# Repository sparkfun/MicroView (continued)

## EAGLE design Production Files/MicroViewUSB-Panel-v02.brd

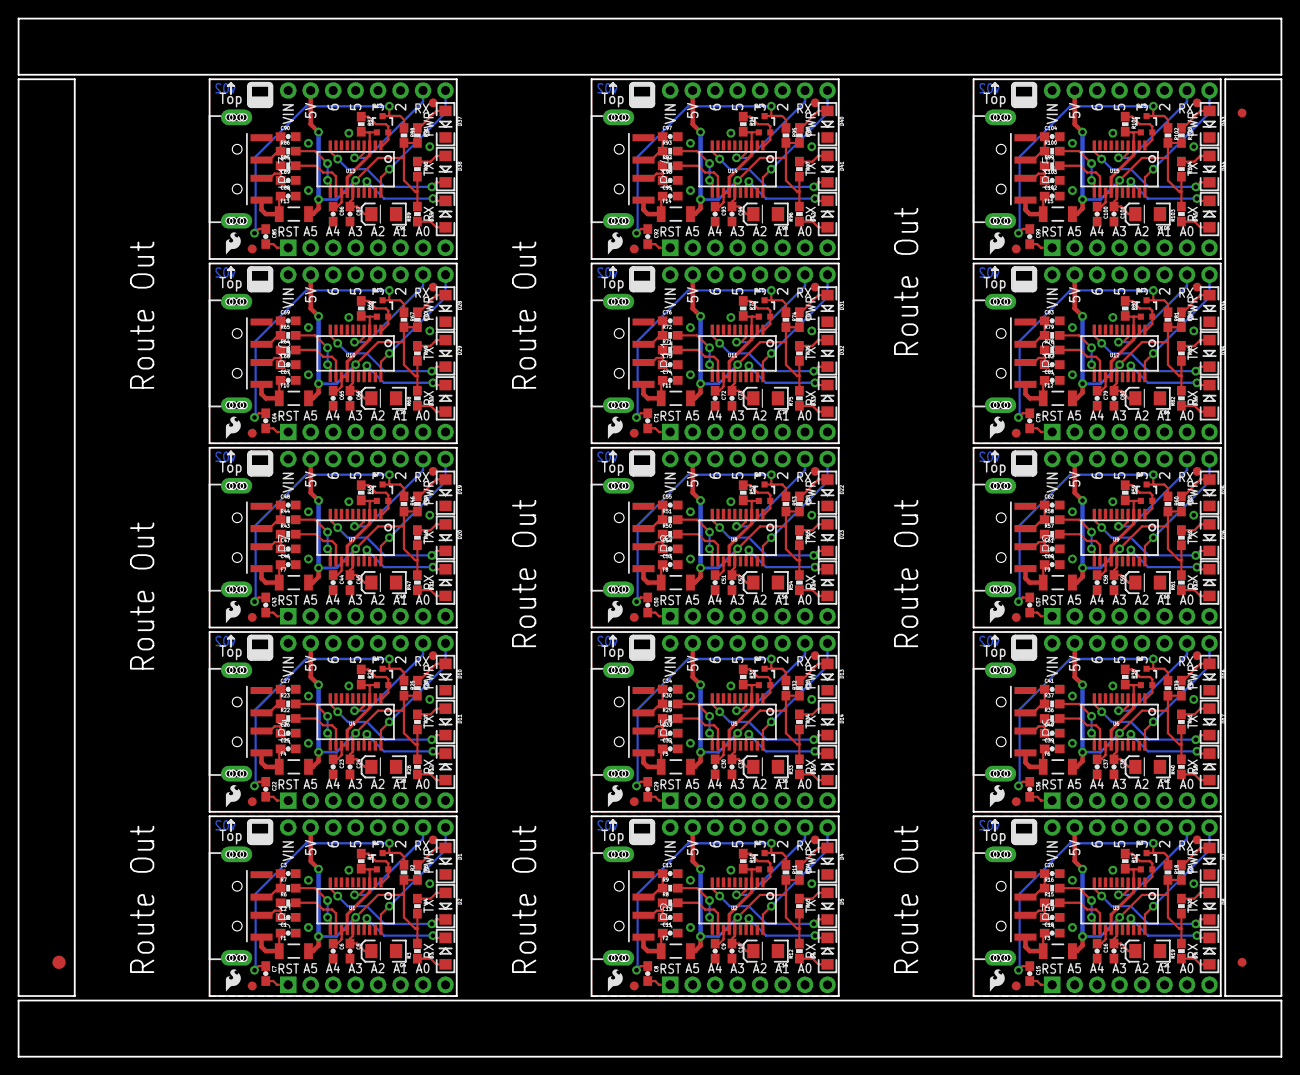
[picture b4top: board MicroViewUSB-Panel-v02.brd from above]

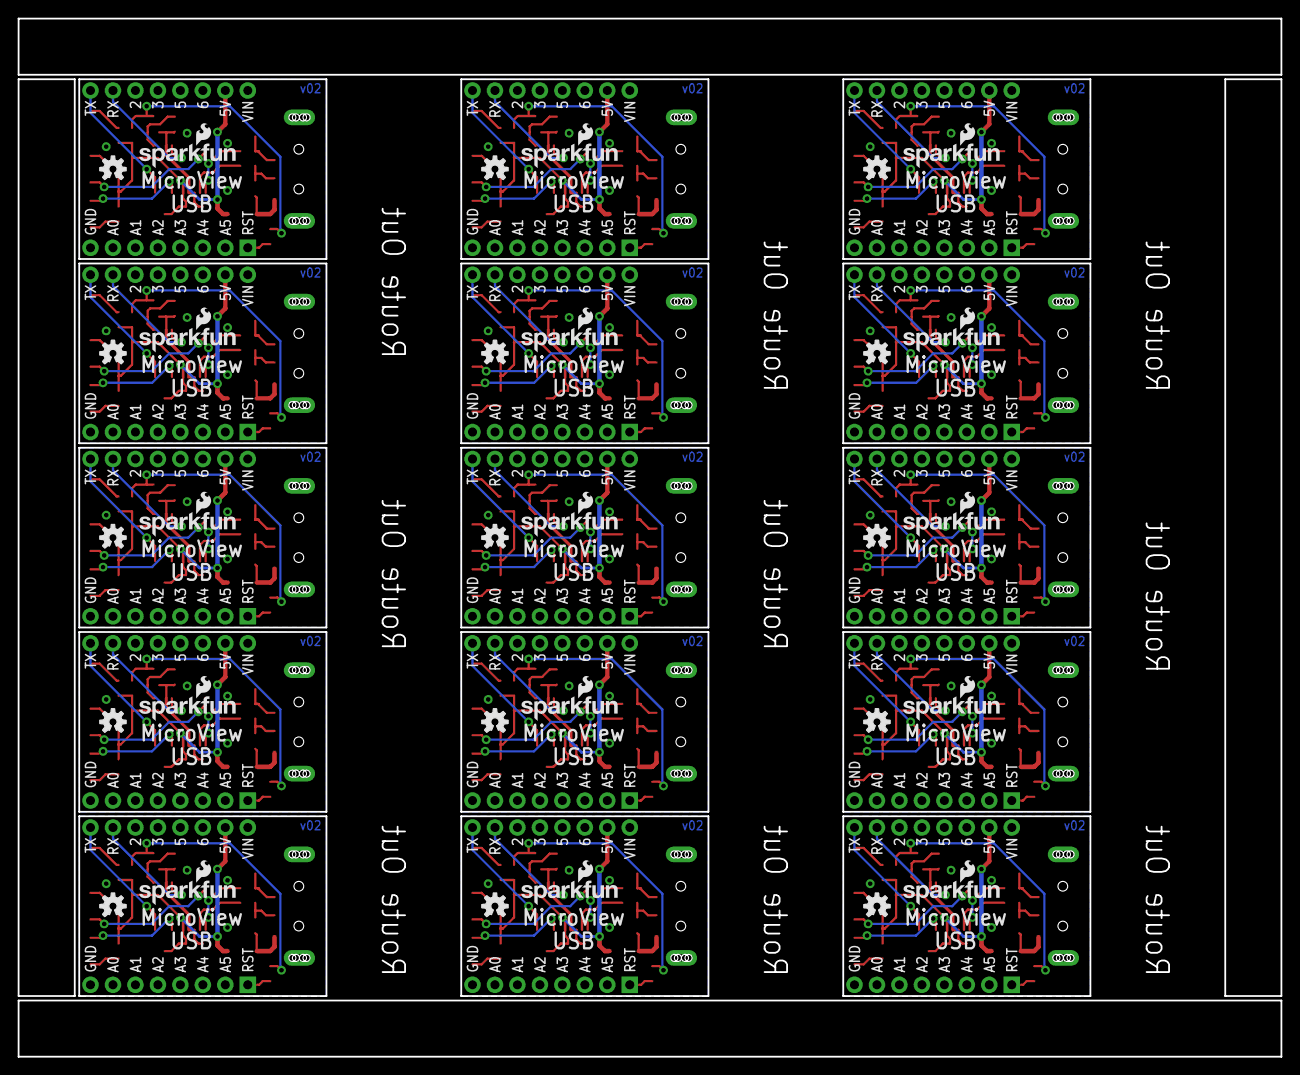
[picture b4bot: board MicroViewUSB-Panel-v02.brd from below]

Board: 2 copper layers, 142.7 x 117.3 mm, 408 parts (30 on the bottom side), 270 nets.

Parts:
C1, C5, C6, C7, C8, C9, C10, C11, C15, C16, C17, C18, C22, C23, C24, C25, C29, C30, C31, C32, C36, C37, C38, C39, C43, C44, C45, C46, C50, C51, C52, C53, C57, C58, C59, C60, C64, C65, C66, C67, C71, C72, C73, C74, C78, C79, C80, C81, C85, C86, C87, C88, C92, C93, C94, C95, C99, C100, C101, C102: 0.1uF; 0603-CAP
C2, C3, C12, C13, C19, C20, C26, C27, C33, C34, C40, C41, C47, C48, C54, C55, C61, C62, C68, C69, C75, C76, C82, C83, C89, C90, C96, C97, C103, C104: 47pF; 0603-CAP
C4, C14, C21, C28, C35, C42, C49, C56, C63, C70, C77, C84, C91, C98, C105: 10uF; EIA3216
D1, D4, D7, D10, D13, D16, D19, D22, D25, D28, D31, D34, D37, D40, D43: GREEN; LED-1206
D2, D5, D8, D11, D14, D17, D20, D23, D26, D29, D32, D35, D38, D41, D44: RED; LED-1206
D3, D6, D9, D12, D15, D18, D21, D24, D27, D30, D33, D36, D39, D42, D45: Yellow; LED-1206
E$1: FIDUCIAL-1.5X3
E$6, E$8: FIDUCIAL-1X2
F1, F2, F3, F4, F5, F6, F7, F8, F9, F10, F11, F12, F13, F14, F15: 500mA; PTC-1206-WIDE
FID1, FID2, FID3, FID4, FID5, FID6, FID7, FID8, FID9, FID10, FID11, FID12, FID13, FID14, FID15, FID16, FID17, FID18, FID19, FID20, FID21, FID22, FID23, FID24, FID25, FID26, FID27, FID28, FID29, FID30: FIDUCIAL1X2; FIDUCIAL-1X2
J1, J2, J3, J4, J5, J6, J7, J8, J9, J10, J11, J12, J13, J14, J15: MICROVIEW-16ND; MV-DIP16-NODIMENSION
JP1, JP2, JP3, JP4, JP5, JP6, JP7, JP8, JP9, JP10, JP11, JP12, JP13, JP14, JP15: USBA-SMD-MALE; USB-A-SMT-MALE
LOGO1, LOGO5, LOGO8, LOGO11, LOGO14, LOGO17, LOGO20, LOGO23, LOGO26, LOGO29, LOGO32, LOGO35, LOGO38, LOGO41, LOGO44: SFE_LOGO_FLAME.1_INCH; SFE_LOGO_FLAME_.1
LOGO2, LOGO4, LOGO7, LOGO10, LOGO13, LOGO16, LOGO19, LOGO22, LOGO25, LOGO28, LOGO31, LOGO34, LOGO37, LOGO40, LOGO43: OSHW-LOGOS; OSHW-LOGO-S
LOGO3, LOGO6, LOGO9, LOGO12, LOGO15, LOGO18, LOGO21, LOGO24, LOGO27, LOGO30, LOGO33, LOGO36, LOGO39, LOGO42, LOGO45: SFE_LOGO_NAME_FLAME.1_INCH; SFE_LOGO_NAME_FLAME_.1
Q1, Q2, Q3, Q4, Q5, Q6, Q7, Q8, Q9, Q10, Q11, Q12, Q13, Q14, Q15: 2N7002PW; SOT323
R1, R2, R10, R11, R17, R18, R24, R25, R31, R32, R38, R39, R45, R46, R52, R53, R59, R60, R66, R67, R73, R74, R80, R81, R87, R88, R94, R95, R101, R102: 10K; 0603-RES
R3, R4, R5, R12, R13, R14, R19, R20, R21, R26, R27, R28, R33, R34, R35, R40, R41, R42, R47, R48, R49, R54, R55, R56, R61, R62, R63, R68, R69, R70, R75, R76, R77, R82, R83, R84, R89, R90, R91, R96, R97, R98, R103, R104, R105: 1K; 0603-RES
R6, R7, R8, R9, R15, R16, R22, R23, R29, R30, R36, R37, R43, R44, R50, R51, R57, R58, R64, R65, R71, R72, R78, R79, R85, R86, R92, R93, R99, R100: 27; 0603-RES
U1, U2, U3, U4, U5, U6, U7, U8, U9, U10, U11, U12, U13, U14, U15: FT231XS; SSOP20_L

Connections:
3.3V: C6.1, Q1.1, R1.2, U1.3, U1.13, U1.14
3.3V1: C9.1, Q2.1, R10.2, U2.3, U2.13, U2.14
3.3V2: C16.1, Q3.1, R17.2, U3.3, U3.13, U3.14
3.3V3: C23.1, Q4.1, R24.2, U4.3, U4.13, U4.14
3.3V4: C30.1, Q5.1, R31.2, U5.3, U5.13, U5.14
3.3V5: C37.1, Q6.1, R38.2, U6.3, U6.13, U6.14
3.3V6: C44.1, Q7.1, R45.2, U7.3, U7.13, U7.14
3.3V7: C51.1, Q8.1, R52.2, U8.3, U8.13, U8.14
3.3V8: C58.1, Q9.1, R59.2, U9.3, U9.13, U9.14
3.3V9: C65.1, Q10.1, R66.2, U10.3, U10.13, U10.14
3.3V10: C72.1, Q11.1, R73.2, U11.3, U11.13, U11.14
3.3V11: C79.1, Q12.1, R80.2, U12.3, U12.13, U12.14
3.3V12: C86.1, Q13.1, R87.2, U13.3, U13.13, U13.14
3.3V13: C93.1, Q14.1, R94.2, U14.3, U14.13, U14.14
3.3V14: C100.1, Q15.1, R101.2, U15.3, U15.13, U15.14
5V: C4.A, C5.1, F1.2, J1.15, R2.2, R3.2, R4.2, R5.2, U1.15
5V1: C10.1, C14.A, F2.2, J2.15, R11.2, R12.2, R13.2, R14.2, U2.15
5V2: C17.1, C21.A, F3.2, J3.15, R18.2, R19.2, R20.2, R21.2, U3.15
5V3: C24.1, C28.A, F4.2, J4.15, R25.2, R26.2, R27.2, R28.2, U4.15
5V4: C31.1, C35.A, F5.2, J5.15, R32.2, R33.2, R34.2, R35.2, U5.15
5V5: C38.1, C42.A, F6.2, J6.15, R39.2, R40.2, R41.2, R42.2, U6.15
5V6: C45.1, C49.A, F7.2, J7.15, R46.2, R47.2, R48.2, R49.2, U7.15
5V7: C52.1, C56.A, F8.2, J8.15, R53.2, R54.2, R55.2, R56.2, U8.15
5V8: C59.1, C63.A, F9.2, J9.15, R60.2, R61.2, R62.2, R63.2, U9.15
5V9: C66.1, C70.A, F10.2, J10.15, R67.2, R68.2, R69.2, R70.2, U10.15
5V10: C73.1, C77.A, F11.2, J11.15, R74.2, R75.2, R76.2, R77.2, U11.15
5V11: C80.1, C84.A, F12.2, J12.15, R81.2, R82.2, R83.2, R84.2, U12.15
5V12: C87.1, C91.A, F13.2, J13.15, R88.2, R89.2, R90.2, R91.2, U13.15
5V13: C94.1, C98.A, F14.2, J14.15, R95.2, R96.2, R97.2, R98.2, U14.15
5V14: C101.1, C105.A, F15.2, J15.15, R102.2, R103.2, R104.2, R105.2, U15.15
D+: C3.1, JP1.D+1, R7.1
D+1: C13.1, JP2.D+1, R9.1
D+2: C20.1, JP3.D+1, R16.1
D+3: C27.1, JP4.D+1, R23.1
D+4: C34.1, JP5.D+1, R30.1
D+5: C41.1, JP6.D+1, R37.1
D+6: C48.1, JP7.D+1, R44.1
D+7: C55.1, JP8.D+1, R51.1
D+8: C62.1, JP9.D+1, R58.1
D+9: C69.1, JP10.D+1, R65.1
D+10: C76.1, JP11.D+1, R72.1
D+11: C83.1, JP12.D+1, R79.1
D+12: C90.1, JP13.D+1, R86.1
D+13: C97.1, JP14.D+1, R93.1
D+14: C104.1, JP15.D+1, R100.1
D-: C2.1, JP1.D-1, R6.1
D-1: C12.1, JP2.D-1, R8.1
D-2: C19.1, JP3.D-1, R15.1
D-3: C26.1, JP4.D-1, R22.1
D-4: C33.1, JP5.D-1, R29.1
D-5: C40.1, JP6.D-1, R36.1
D-6: C47.1, JP7.D-1, R43.1
D-7: C54.1, JP8.D-1, R50.1
D-8: C61.1, JP9.D-1, R57.1
D-9: C68.1, JP10.D-1, R64.1
D-10: C75.1, JP11.D-1, R71.1
D-11: C82.1, JP12.D-1, R78.1
D-12: C89.1, JP13.D-1, R85.1
D-13: C96.1, JP14.D-1, R92.1
D-14: C103.1, JP15.D-1, R99.1
DTR: C7.1, Q1.3, R2.1
DTR1: C8.1, Q2.3, R11.1
DTR2: C15.1, Q3.3, R18.1
DTR3: C22.1, Q4.3, R25.1
DTR4: C29.1, Q5.3, R32.1
DTR5: C36.1, Q6.3, R39.1
DTR6: C43.1, Q7.3, R46.1
DTR7: C50.1, Q8.3, R53.1
DTR8: C57.1, Q9.3, R60.1
DTR9: C64.1, Q10.3, R67.1
DTR10: C71.1, Q11.3, R74.1
DTR11: C78.1, Q12.3, R81.1
DTR12: C85.1, Q13.3, R88.1
DTR13: C92.1, Q14.3, R95.1
DTR14: C99.1, Q15.3, R102.1
GND: C1.2, C2.2, C3.2, C4.C, C5.2, C6.2, D1.C, J1.8, JP1.GND1, U1.6, U1.16
GND1: C9.2, C10.2, C11.2, C12.2, C13.2, C14.C, D4.C, J2.8, JP2.GND1, U2.6, U2.16
GND2: C16.2, C17.2, C18.2, C19.2, C20.2, C21.C, D7.C, J3.8, JP3.GND1, U3.6, U3.16
GND3: C23.2, C24.2, C25.2, C26.2, C27.2, C28.C, D10.C, J4.8, JP4.GND1, U4.6, U4.16
GND4: C30.2, C31.2, C32.2, C33.2, C34.2, C35.C, D13.C, J5.8, JP5.GND1, U5.6, U5.16
GND5: C37.2, C38.2, C39.2, C40.2, C41.2, C42.C, D16.C, J6.8, JP6.GND1, U6.6, U6.16
GND6: C44.2, C45.2, C46.2, C47.2, C48.2, C49.C, D19.C, J7.8, JP7.GND1, U7.6, U7.16
GND7: C51.2, C52.2, C53.2, C54.2, C55.2, C56.C, D22.C, J8.8, JP8.GND1, U8.6, U8.16
GND8: C58.2, C59.2, C60.2, C61.2, C62.2, C63.C, D25.C, J9.8, JP9.GND1, U9.6, U9.16
GND9: C65.2, C66.2, C67.2, C68.2, C69.2, C70.C, D28.C, J10.8, JP10.GND1, U10.6, U10.16
GND10: C72.2, C73.2, C74.2, C75.2, C76.2, C77.C, D31.C, J11.8, JP11.GND1, U11.6, U11.16
GND11: C79.2, C80.2, C81.2, C82.2, C83.2, C84.C, D34.C, J12.8, JP12.GND1, U12.6, U12.16
GND12: C86.2, C87.2, C88.2, C89.2, C90.2, C91.C, D37.C, J13.8, JP13.GND1, U13.6, U13.16
GND13: C93.2, C94.2, C95.2, C96.2, C97.2, C98.C, D40.C, J14.8, JP14.GND1, U14.6, U14.16
GND14: C100.2, C101.2, C102.2, C103.2, C104.2, C105.C, D43.C, J15.8, JP15.GND1, U15.6, U15.16
unnamed: D1.A, R5.1
unnamed: C7.2, J1.1
unnamed: D5.A, R13.1
unnamed: D6.A, R12.1
unnamed: R8.2, U2.12
unnamed: R6.2, U1.12
unnamed: R7.2, U1.11
unnamed: D2.A, R4.1
unnamed: R9.2, U2.11
unnamed: D3.A, R3.1
unnamed: Q2.2, R10.1, U2.1
unnamed: Q1.2, R1.1, U1.1
unnamed: D4.A, R14.1
unnamed: C8.2, J2.1
unnamed: D8.A, R20.1
unnamed: D9.A, R19.1
unnamed: R15.2, U3.12
unnamed: R16.2, U3.11
unnamed: Q3.2, R17.1, U3.1
unnamed: D7.A, R21.1
unnamed: C15.2, J3.1
unnamed: D11.A, R27.1
unnamed: D12.A, R26.1
unnamed: R22.2, U4.12
unnamed: R23.2, U4.11
unnamed: Q4.2, R24.1, U4.1
unnamed: D10.A, R28.1
unnamed: C22.2, J4.1
unnamed: D14.A, R34.1
unnamed: D15.A, R33.1
unnamed: R29.2, U5.12
unnamed: R30.2, U5.11
unnamed: Q5.2, R31.1, U5.1
unnamed: D13.A, R35.1
unnamed: C29.2, J5.1
unnamed: D17.A, R41.1
unnamed: D18.A, R40.1
unnamed: R36.2, U6.12
unnamed: R37.2, U6.11
unnamed: Q6.2, R38.1, U6.1
unnamed: D16.A, R42.1
unnamed: C36.2, J6.1
unnamed: D20.A, R48.1
unnamed: D21.A, R47.1
unnamed: R43.2, U7.12
unnamed: R44.2, U7.11
unnamed: Q7.2, R45.1, U7.1
unnamed: D19.A, R49.1
unnamed: C43.2, J7.1
unnamed: D23.A, R55.1
unnamed: D24.A, R54.1
unnamed: R50.2, U8.12
unnamed: R51.2, U8.11
unnamed: Q8.2, R52.1, U8.1
unnamed: D22.A, R56.1
unnamed: C50.2, J8.1
unnamed: D26.A, R62.1
unnamed: D27.A, R61.1
unnamed: R57.2, U9.12
unnamed: R58.2, U9.11
unnamed: Q9.2, R59.1, U9.1
unnamed: D25.A, R63.1
unnamed: C57.2, J9.1
unnamed: D29.A, R69.1
unnamed: D30.A, R68.1
unnamed: R64.2, U10.12
unnamed: R65.2, U10.11
unnamed: Q10.2, R66.1, U10.1
unnamed: D28.A, R70.1
unnamed: C64.2, J10.1
unnamed: D32.A, R76.1
unnamed: D33.A, R75.1
unnamed: R71.2, U11.12
unnamed: R72.2, U11.11
unnamed: Q11.2, R73.1, U11.1
unnamed: D31.A, R77.1
unnamed: C71.2, J11.1
unnamed: D35.A, R83.1
unnamed: D36.A, R82.1
unnamed: R78.2, U12.12
unnamed: R79.2, U12.11
unnamed: Q12.2, R80.1, U12.1
unnamed: D34.A, R84.1
unnamed: C78.2, J12.1
unnamed: D38.A, R90.1
unnamed: D39.A, R89.1
unnamed: R85.2, U13.12
unnamed: R86.2, U13.11
unnamed: Q13.2, R87.1, U13.1
unnamed: D37.A, R91.1
unnamed: C85.2, J13.1
unnamed: D41.A, R97.1
unnamed: D42.A, R96.1
unnamed: R92.2, U14.12
unnamed: R93.2, U14.11
unnamed: Q14.2, R94.1, U14.1
unnamed: D40.A, R98.1
unnamed: C92.2, J14.1
unnamed: D44.A, R104.1
unnamed: D45.A, R103.1
unnamed: R99.2, U15.12
unnamed: R100.2, U15.11
unnamed: Q15.2, R101.1, U15.1
unnamed: D43.A, R105.1
unnamed: C99.2, J15.1
RXD: J1.10, U1.4
RXD1: J2.10, U2.4
RXD2: J3.10, U3.4
RXD3: J4.10, U4.4
RXD4: J5.10, U5.4
RXD5: J6.10, U6.4
RXD6: J7.10, U7.4
RXD7: J8.10, U8.4
RXD8: J9.10, U9.4
RXD9: J10.10, U10.4
RXD10: J11.10, U11.4
RXD11: J12.10, U12.4
RXD12: J13.10, U13.4
RXD13: J14.10, U14.4
RXD14: J15.10, U15.4
RXLED: D3.C, U1.17
RXLED1: D6.C, U2.17
RXLED2: D9.C, U3.17
RXLED3: D12.C, U4.17
RXLED4: D15.C, U5.17
RXLED5: D18.C, U6.17
RXLED6: D21.C, U7.17
RXLED7: D24.C, U8.17
RXLED8: D27.C, U9.17
RXLED9: D30.C, U10.17
RXLED10: D33.C, U11.17
RXLED11: D36.C, U12.17
RXLED12: D39.C, U13.17
RXLED13: D42.C, U14.17
RXLED14: D45.C, U15.17
TXD: J1.9, U1.20
TXD1: J2.9, U2.20
TXD2: J3.9, U3.20
TXD3: J4.9, U4.20
TXD4: J5.9, U5.20
TXD5: J6.9, U6.20
TXD6: J7.9, U7.20
TXD7: J8.9, U8.20
TXD8: J9.9, U9.20
TXD9: J10.9, U10.20
TXD10: J11.9, U11.20
TXD11: J12.9, U12.20
TXD12: J13.9, U13.20
TXD13: J14.9, U14.20
TXD14: J15.9, U15.20
TXLED: D2.C, U1.10
TXLED1: D5.C, U2.10
TXLED2: D8.C, U3.10
TXLED3: D11.C, U4.10
TXLED4: D14.C, U5.10
TXLED5: D17.C, U6.10
TXLED6: D20.C, U7.10
TXLED7: D23.C, U8.10
TXLED8: D26.C, U9.10
TXLED9: D29.C, U10.10
TXLED10: D32.C, U11.10
TXLED11: D35.C, U12.10
TXLED12: D38.C, U13.10
TXLED13: D41.C, U14.10
TXLED14: D44.C, U15.10
VUSB: C1.1, F1.1, JP1.VBUS1
VUSB1: C11.1, F2.1, JP2.VBUS1
VUSB2: C18.1, F3.1, JP3.VBUS1
VUSB3: C25.1, F4.1, JP4.VBUS1
VUSB4: C32.1, F5.1, JP5.VBUS1
VUSB5: C39.1, F6.1, JP6.VBUS1
VUSB6: C46.1, F7.1, JP7.VBUS1
VUSB7: C53.1, F8.1, JP8.VBUS1
VUSB8: C60.1, F9.1, JP9.VBUS1
VUSB9: C67.1, F10.1, JP10.VBUS1
VUSB10: C74.1, F11.1, JP11.VBUS1
VUSB11: C81.1, F12.1, JP12.VBUS1
VUSB12: C88.1, F13.1, JP13.VBUS1
VUSB13: C95.1, F14.1, JP14.VBUS1
VUSB14: C102.1, F15.1, JP15.VBUS1
